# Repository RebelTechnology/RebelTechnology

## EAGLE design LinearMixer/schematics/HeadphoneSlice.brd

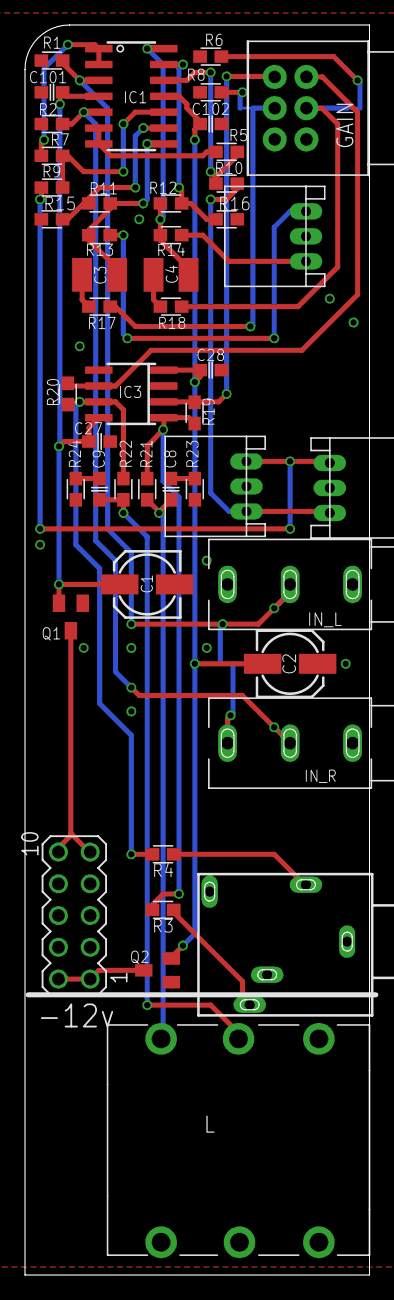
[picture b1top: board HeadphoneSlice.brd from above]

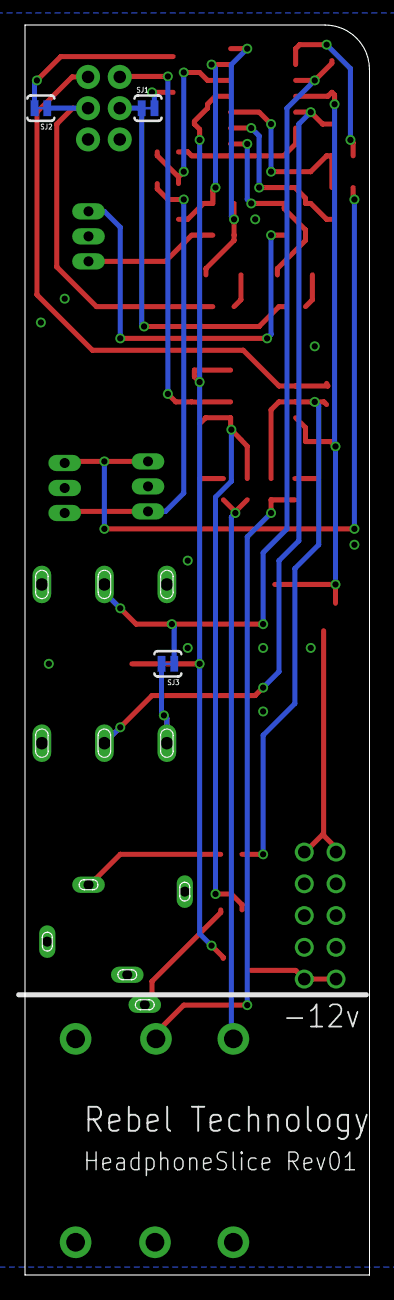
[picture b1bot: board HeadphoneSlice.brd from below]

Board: 2 copper layers, 27.5 x 100.0 mm, 50 parts (3 on the bottom side), 36 nets.

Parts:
3I, 3O, 3O2: CON-JST_PH_3W
C1, C2: 10u; 153CLV-0505
C3, C4: 1u Polyester; C1210
C8, C9: 47n; C0603
C27, C28, C101, C102: 100n; C0603
GAIN: POT-BOURNS-PTD902
IC1: QUAD_OPAMPD; SO14
IC3: RC4560; SO08
IN_L: JACK-UJ-3502-RSLOT; UJ-3502-R-SLOT
IN_R: JACK-UJ-3502-RSLOT; UJ-3502-R-SLOT
L: NEUTRIK_NMJ6HCD2; NMJ6HCD2
Q1: SI2309CDS; SOT23
Q2: BSS123; SOT23
R1, R2: 1M; 0603
R3, R4: 100R; 0603
R5, R7, R9, R10: 100k; 0603
R6, R8: 2k7; 0603
R11, R12, R15, R16, R19, R20: 10k; 0603
R13, R14: 1k; 0603
R17, R18: 22k; 0603
R21, R22: 22R; 0603
R23, R24: 10R; 0603
SJ1, SJ2, SJ3: SOLDERJUMPERTRACE; SJ_2S-TRACE
SV1: MA05-2
X1: 1503_09

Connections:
+12V: C1.+, C27.1, C101.1, IC1.4, IC3.8, Q1.2
-12V: C2.-, C28.1, C102.1, IC1.11, IC3.4, Q2.2
BUS_IN_L: 3I.P3, 3O.P1, R9.2
BUS_IN_R: 3I.P1, 3O.P3, R10.2
BUS_OUT_L: 3O2.P1, R13.2
BUS_OUT_R: 3O2.P3, R14.2
GND: 3I.P2, 3O.P2, 3O2.P2, C1.-, C2.+, C27.2, C28.2, C101.2, C102.2, GAIN.1, GAIN.4, IC3.3, IC3.5, IN_L.P$3, IN_R.P$3, L.S, L.SN, Q1.1, Q2.1, R1.2, R2.2, R6.2, R8.2, R15.1, R16.1, R23.1, R24.1, SV1.3, SV1.4, SV1.5, SV1.6, SV1.7, SV1.8, X1.1
HP_L: C8.1, L.T, R21.1
HP_R: C9.1, L.R, R22.1
IN_B1: IN_R.P$2, SJ3.2
IN_L: IC1.3, IN_L.P$1, R1.1, SJ3.1
IN_R: IC1.5, IN_R.P$1, R2.1
LINE_L: R3.1, X1.3
LINE_R: R4.1, X1.2
unnamed: Q2.3, SV1.1, SV1.2
unnamed: IC3.7, R4.2, R20.1, R22.2
unnamed: GAIN.6, IC3.2, R19.2
unnamed: C4.2, R18.2
unnamed: GAIN.5, R17.1, SJ1.1
unnamed: GAIN.2, R18.1, SJ2.1
unnamed: C4.1, IC1.14, R12.2, R14.1
unnamed: C3.2, R17.2
unnamed: R8.1, SJ1.2
unnamed: C3.1, IC1.8, R11.2, R13.1
unnamed: IC1.6, IC1.7, R5.2
unnamed: C9.2, R24.2
unnamed: IC1.1, IC1.2, R7.2
unnamed: Q1.3, SV1.9, SV1.10
unnamed: R6.1, SJ2.2
unnamed: GAIN.3, IC3.6, R20.2
unnamed: IC1.9, R11.1, R15.2
unnamed: IC1.13, R12.1, R16.2
unnamed: IC3.1, R3.2, R19.1, R21.2
unnamed: C8.2, R23.2
unnamed: IC1.12, R5.1, R10.1
unnamed: IC1.10, R7.1, R9.1

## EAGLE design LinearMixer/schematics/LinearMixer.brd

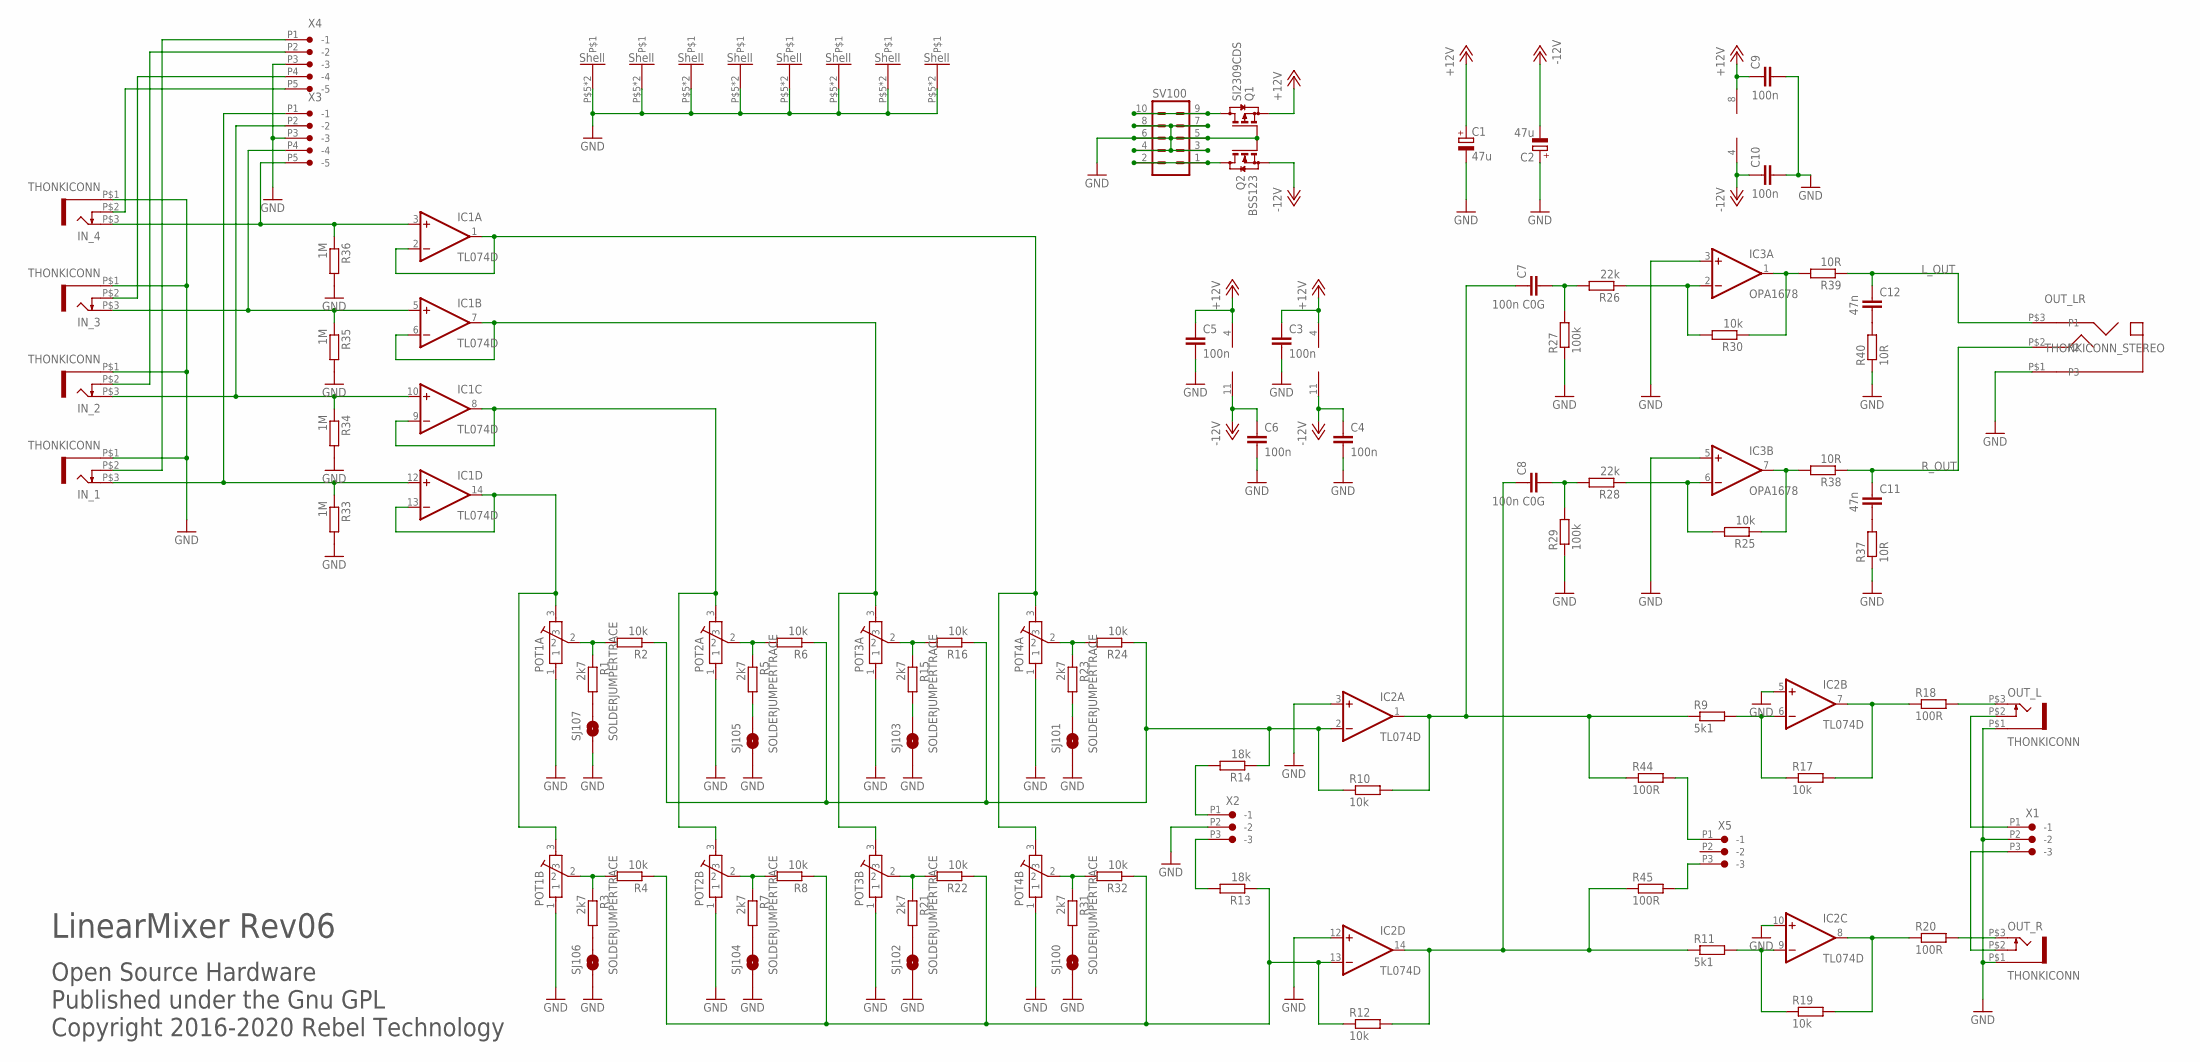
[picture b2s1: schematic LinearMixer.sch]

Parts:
C1, C2: 47u; 153CLV-0505
C3, C4, C5, C6, C9, C10: 100n; C0603
C7, C8: 100n C0G; C1210
C11, C12: 47n; C0603
IC1, IC2: TL074D; SO14
IC3: OPA1678; SO08
IN_1, IN_2, IN_3, IN_4: THONKICONN
OUT_L: THONKICONN
OUT_LR: THONKICONN_STEREO
OUT_R: THONKICONN
POT1A, POT1B, POT2A, POT2B, POT3A, POT3B, POT4A, POT4B: POT-ALPS-RK09L1140
Q1: SI2309CDS; SOT23
Q2: BSS123; SOT23
R1, R3, R5, R7, R15, R21, R23, R31: 2k7; 0603
R2, R4, R6, R8, R10, R12, R16, R17, R19, R22, R24, R25, R30, R32: 10k; 0603
R9, R11: 5k1; 0603
R13, R14: 18k; 0603
R18, R20, R44, R45: 100R; 0603
R26, R28: 22k; 0603
R27, R29: 100k; 0603
R33, R34, R35, R36: 1M; 0603
R37, R38, R39, R40: 10R; 0603
SJ100, SJ101, SJ102, SJ103, SJ104, SJ105, SJ106, SJ107: SOLDERJUMPERTRACE; SJ_2S-TRACE
SV100: MA05-2
X1, X2, X5: CON-JST_PH_3W
X3, X4: CON-JST_PH_5W

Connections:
+12V: C1.+, C3.1, C5.1, C9.1, IC1.4 (V+), IC2.4 (V+), IC3.8 (V+), Q1.2 (S)
-12V: C2.-, C4.1, C6.1, C10.1, IC1.11 (V-), IC2.11 (V-), IC3.4 (V-), Q2.2 (S)
GND: C1.-, C2.+, C3.2, C4.2, C5.2, C6.2, C9.2, C10.2, IC2.3 (+IN), IC2.5 (+IN), IC2.10 (+IN), IC2.12 (+IN), IC3.3 (+IN), IC3.5 (+IN), IN_1.P$1 (5), IN_2.P$1 (5), IN_3.P$1 (5), IN_4.P$1 (5), OUT_L.P$1 (5), OUT_LR.P$1 (P3), OUT_R.P$1 (5), POT1A.1, POT1A.P$5, POT1A.P$6, POT1B.1, POT1B.P$5, POT1B.P$6, POT2A.1, POT2A.P$5, POT2A.P$6, POT2B.1, POT2B.P$5, POT2B.P$6, POT3A.1, POT3A.P$5, POT3A.P$6, POT3B.1, POT3B.P$5, POT3B.P$6, POT4A.1, POT4A.P$5, POT4A.P$6, POT4B.1, POT4B.P$5, POT4B.P$6, Q1.1 (G), Q2.1 (G), R27.1, R29.1, R33.2, R34.2, R35.2, R36.2, R37.1, R40.1, SJ100.1, SJ101.1, SJ102.1, SJ103.1, SJ104.1, SJ105.1, SJ106.1, SJ107.1, SV100.3, SV100.4, SV100.5, SV100.6, SV100.7, SV100.8, X1.P2 (-2), X2.P2 (-2), X3.P3 (-3), X4.P3 (-3)
IN_1: IC1.12 (+IN), IN_1.P$3 (3), R33.1, X3.P1 (-1)
IN_2: IC1.10 (+IN), IN_2.P$3 (3), R34.1, X3.P2 (-2)
IN_3: IC1.5 (+IN), IN_3.P$3 (3), R35.1, X3.P4 (-4)
IN_4: IC1.3 (+IN), IN_4.P$3 (3), R36.1, X3.P5 (-5)
IN_A: R14.2, X2.P1 (-1)
IN_B: R13.2, X2.P3 (-3)
IN_SW_1: IN_1.P$2 (4), X4.P1 (-1)
IN_SW_2: IN_2.P$2 (4), X4.P2 (-2)
IN_SW_3: IN_3.P$2 (4), X4.P4 (-4)
IN_SW_4: IN_4.P$2 (4), X4.P5 (-5)
L_OUT: C12.1, OUT_LR.P$3 (P1), R39.1
unnamed: Q2.3 (D), SV100.1, SV100.2
unnamed: IC3.7 (OUT), R25.1, R38.2
unnamed: IC3.2 (-IN), R26.1, R30.2
unnamed: C8.2, R28.2, R29.2
unnamed: IC2.8 (OUT), R19.2, R20.1
unnamed: IC2.7 (OUT), R17.2, R18.1
unnamed: IC2.13 (-IN), R4.1, R8.1, R12.1, R13.1, R22.1, R32.1
unnamed: C7.2, R26.2, R27.2
unnamed: OUT_L.P$3 (3), R18.2
unnamed: C8.1, IC2.14 (OUT), R11.1, R12.2, R45.1
unnamed: IC2.2 (-IN), R2.1, R6.1, R10.1, R14.1, R16.1, R24.1
unnamed: C11.2, R37.2
unnamed: C7.1, IC2.1 (OUT), R9.1, R10.2, R44.1
unnamed: Q1.3 (D), SV100.9, SV100.10
unnamed: OUT_R.P$3 (3), R20.2
unnamed: IC3.6 (-IN), R25.2, R28.1
unnamed: R1.2, SJ107.2
unnamed: IC2.6 (-IN), R9.2, R17.1
unnamed: IC3.1 (OUT), R30.1, R39.2
unnamed: POT1B.2, R3.1, R4.2
unnamed: C12.2, R40.2
unnamed: R5.2, SJ105.2
unnamed: IC2.9 (-IN), R11.2, R19.1
unnamed: R15.2, SJ103.2
unnamed: R23.2, SJ101.2
unnamed: R3.2, SJ106.2
unnamed: IC1.8 (OUT), IC1.9 (-IN), POT2A.3, POT2B.3
unnamed: R7.2, SJ104.2
unnamed: POT1A.2, R1.1, R2.2
unnamed: POT2B.2, R7.1, R8.2
unnamed: POT3B.2, R21.1, R22.2
unnamed: R21.2, SJ102.2
unnamed: R31.2, SJ100.2
unnamed: IC1.13 (-IN), IC1.14 (OUT), POT1A.3, POT1B.3
unnamed: POT4B.2, R31.1, R32.2
unnamed: POT4A.2, R23.1, R24.2
unnamed: POT3A.2, R15.1, R16.2
unnamed: POT2A.2, R5.1, R6.2
unnamed: IC1.6 (-IN), IC1.7 (OUT), POT3A.3, POT3B.3
unnamed: IC1.1 (OUT), IC1.2 (-IN), POT4A.3, POT4B.3
OUT_NS_L: R44.2, X5.P1 (-1)
OUT_NS_R: R45.2, X5.P3 (-3)
OUT_SW_A: OUT_L.P$2 (4), X1.P1 (-1)
OUT_SW_B: OUT_R.P$2 (4), X1.P3 (-3)
R_OUT: C11.1, OUT_LR.P$2 (P2), R38.1

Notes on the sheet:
Open Source Hardware Published under the Gnu GPL Copyright 2016-2020 Rebel Technology
LinearMixer Rev06

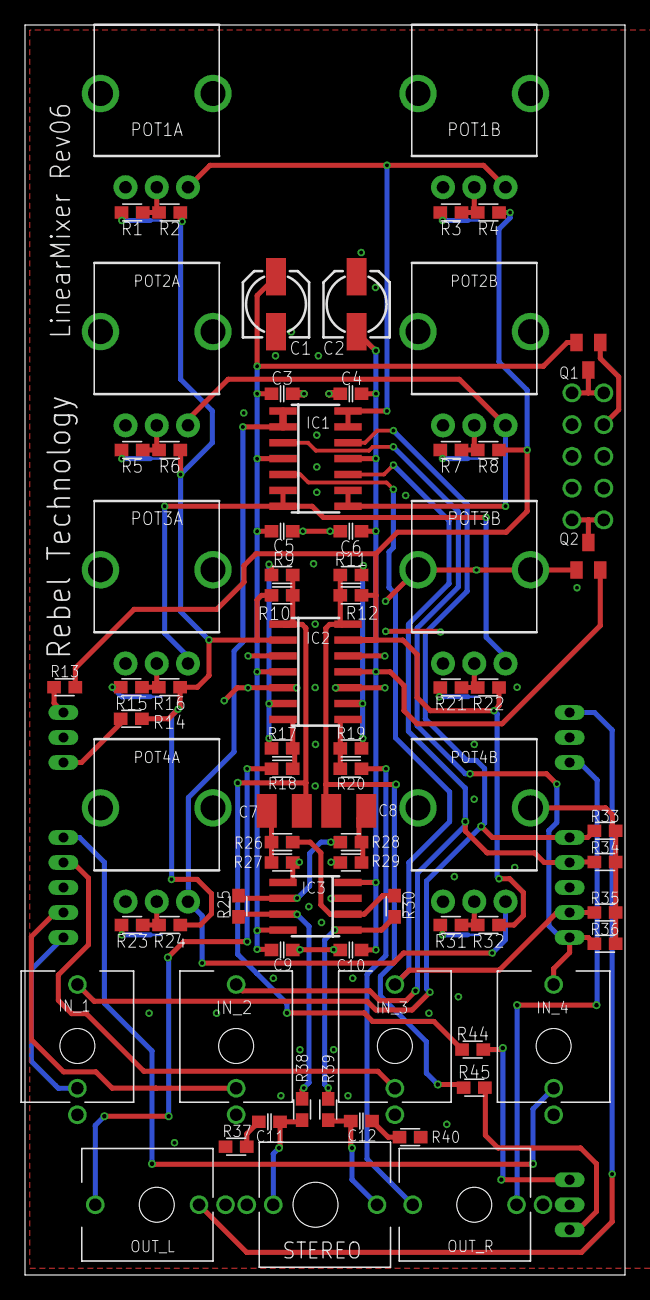
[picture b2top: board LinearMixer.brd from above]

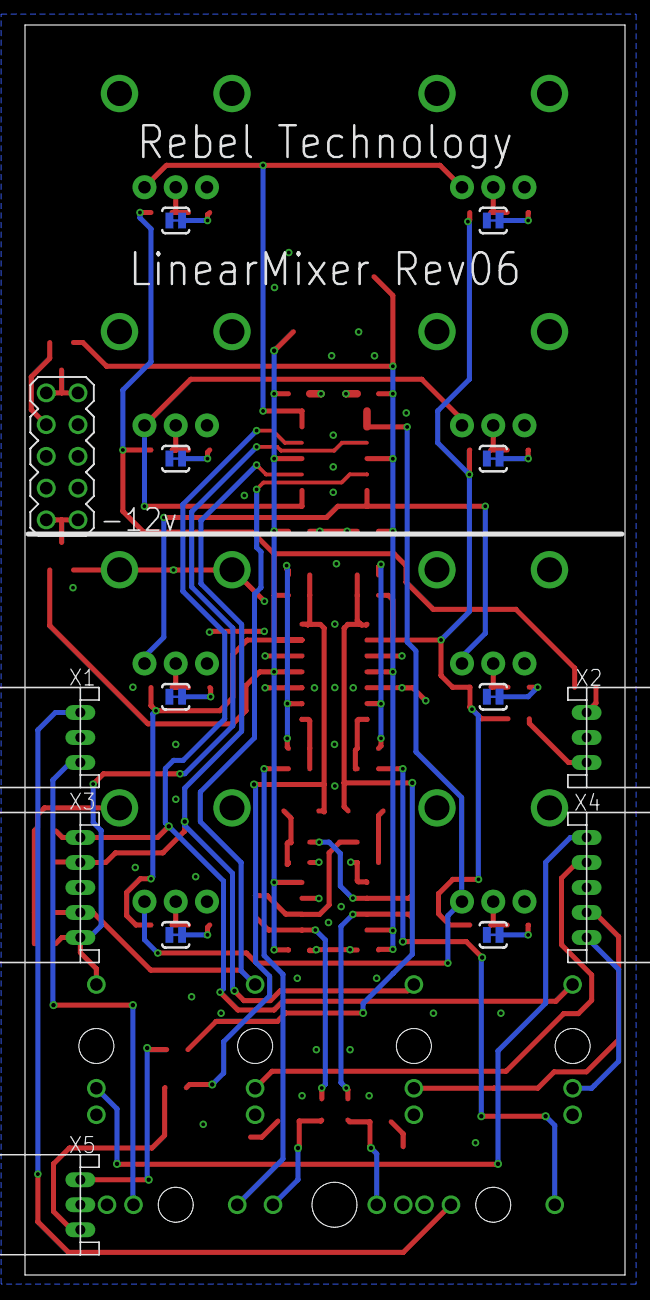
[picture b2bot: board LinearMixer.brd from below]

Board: 2 copper layers, 48.0 x 100.0 mm, 88 parts (14 on the bottom side), 59 nets.

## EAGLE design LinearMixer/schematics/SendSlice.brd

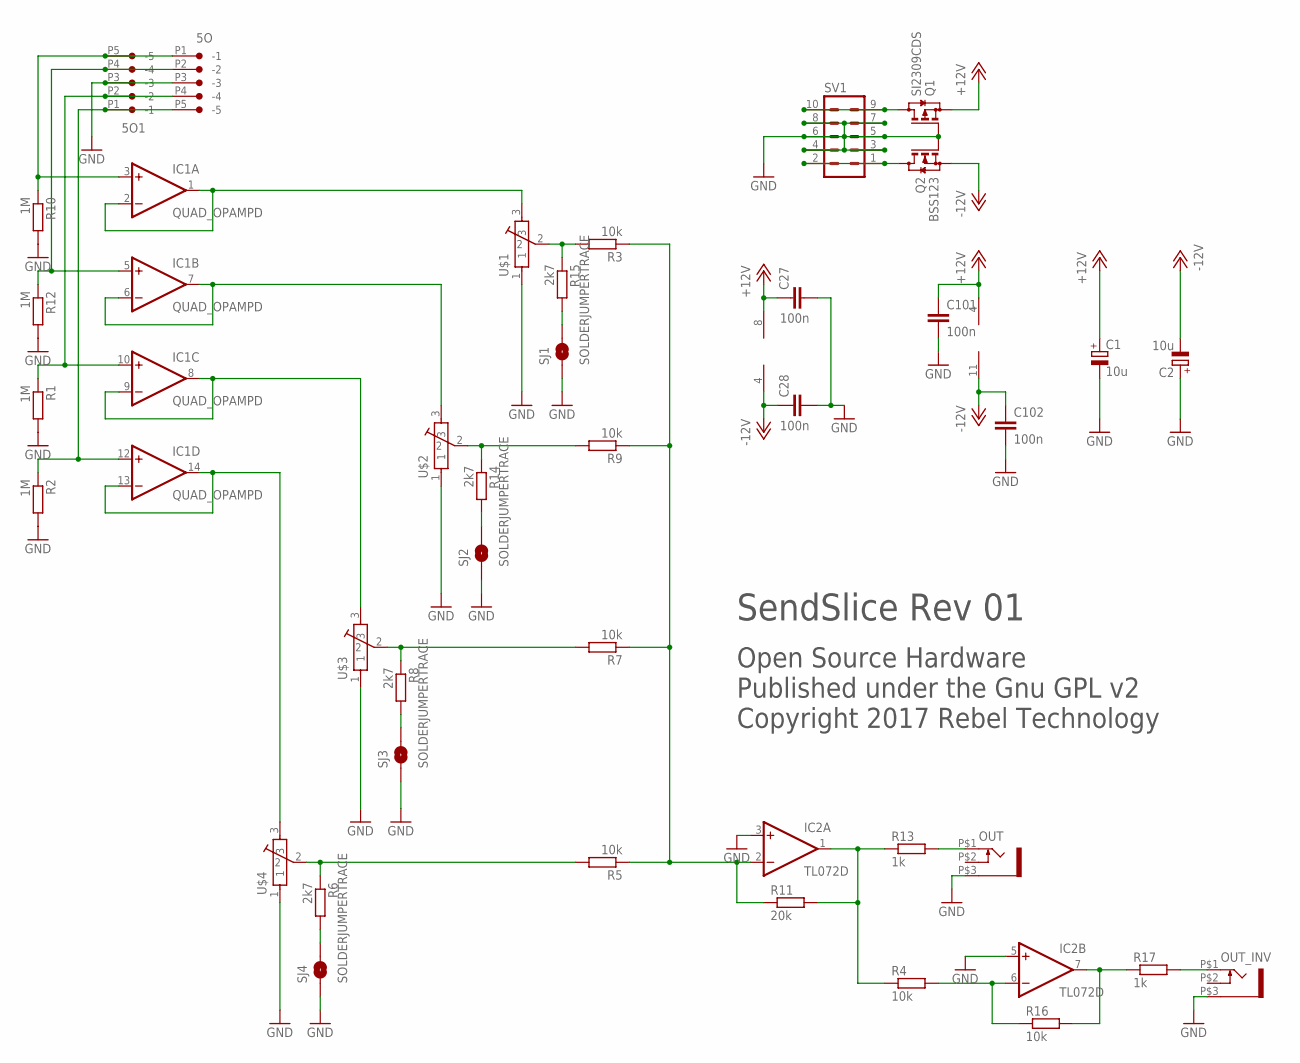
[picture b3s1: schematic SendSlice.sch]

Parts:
5O, 5O1: CON-JST_PH_5W
C1, C2: 10u; 153CLV-0505
C27, C28, C101, C102: 100n; C0603
IC1: QUAD_OPAMPD; SO14
IC2: TL072D; SO08
OUT: JACK-UJ-3502-R; UJ-3502-R
OUT_INV: JACK-UJ-3502-R; UJ-3502-R
Q1: SI2309CDS; SOT23
Q2: BSS123; SOT23
R1, R2, R10, R12: 1M; 0603
R3, R4, R5, R7, R9, R16: 10k; 0603
R6, R8, R14, R15: 2k7; 0603
R11: 20k; 0603
R13, R17: 1k; 0603
SJ1, SJ2, SJ3, SJ4: SOLDERJUMPERTRACE; SJ_2S-TRACE
SV1: MA05-2
U$1, U$2, U$3, U$4: POT-BOURNS-PTD901

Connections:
+12V: C1.+, C27.1, C101.1, IC1.4 (V+), IC2.8 (V+), Q1.2 (S)
-12V: C2.-, C28.1, C102.1, IC1.11 (V-), IC2.4 (V-), Q2.2 (S)
GND: 5O.P3 (-3), 5O1.P3 (-3), C1.-, C2.+, C27.2, C28.2, C101.2, C102.2, IC2.3 (+IN), IC2.5 (+IN), OUT.P$3 (SLEEVE), OUT_INV.P$3 (SLEEVE), Q1.1 (G), Q2.1 (G), R1.2, R2.2, R10.2, R12.2, SJ1.1, SJ2.1, SJ3.1, SJ4.1, SV1.3, SV1.4, SV1.5, SV1.6, SV1.7, SV1.8, U$1.1, U$2.1, U$3.1, U$4.1
IN_1: 5O.P5 (-5), 5O1.P1 (-1), IC1.12 (+IN), R2.1
IN_2: 5O.P4 (-4), 5O1.P2 (-2), IC1.10 (+IN), R1.1
IN_3: 5O.P2 (-2), 5O1.P4 (-4), IC1.5 (+IN), R12.1
IN_4: 5O.P1 (-1), 5O1.P5 (-5), IC1.3 (+IN), R10.1
unnamed: Q2.3 (D), SV1.1, SV1.2
unnamed: R9.2, R14.1, U$2.2
unnamed: R3.2, R15.1, U$1.2
unnamed: IC1.6 (-IN), IC1.7 (OUT), U$2.3
unnamed: IC1.1 (OUT), IC1.2 (-IN), U$1.3
unnamed: IC2.1 (OUT), R4.1, R11.2, R13.1
unnamed: IC2.7 (OUT), R16.2, R17.1
unnamed: IC2.2 (-IN), R3.1, R5.1, R7.1, R9.1, R11.1
unnamed: OUT.P$1 (TIP), R13.2
unnamed: R15.2, SJ1.2
unnamed: IC1.13 (-IN), IC1.14 (OUT), U$4.3
unnamed: R6.2, SJ4.2
unnamed: IC1.8 (OUT), IC1.9 (-IN), U$3.3
unnamed: Q1.3 (D), SV1.9, SV1.10
unnamed: R8.2, SJ3.2
unnamed: R14.2, SJ2.2
unnamed: IC2.6 (-IN), R4.2, R16.1
unnamed: OUT_INV.P$1 (TIP), R17.2
unnamed: R5.2, R6.1, U$4.2
unnamed: R7.2, R8.1, U$3.2

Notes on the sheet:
Open Source Hardware Published under the Gnu GPL v2 Copyright 2017 Rebel Technology
SendSlice Rev 01

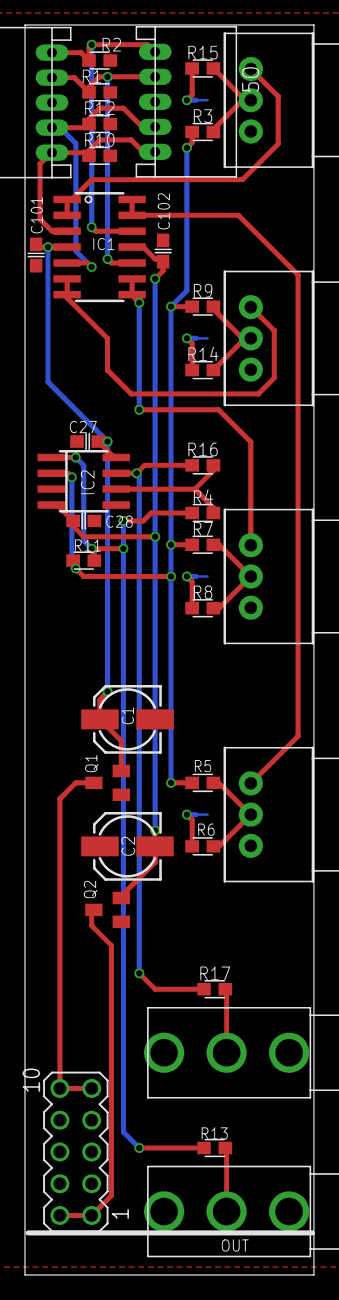
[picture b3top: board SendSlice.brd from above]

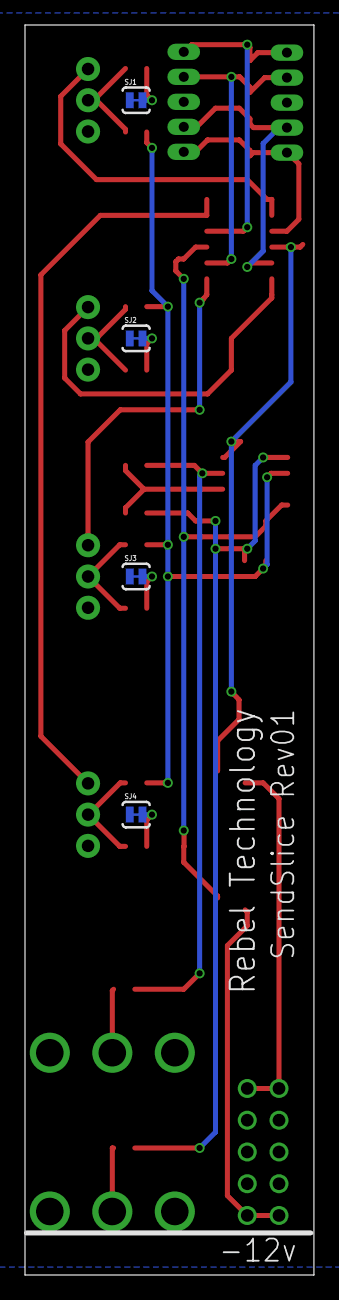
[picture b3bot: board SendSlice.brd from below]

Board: 2 copper layers, 23.1 x 100.0 mm, 40 parts (4 on the bottom side), 27 nets.

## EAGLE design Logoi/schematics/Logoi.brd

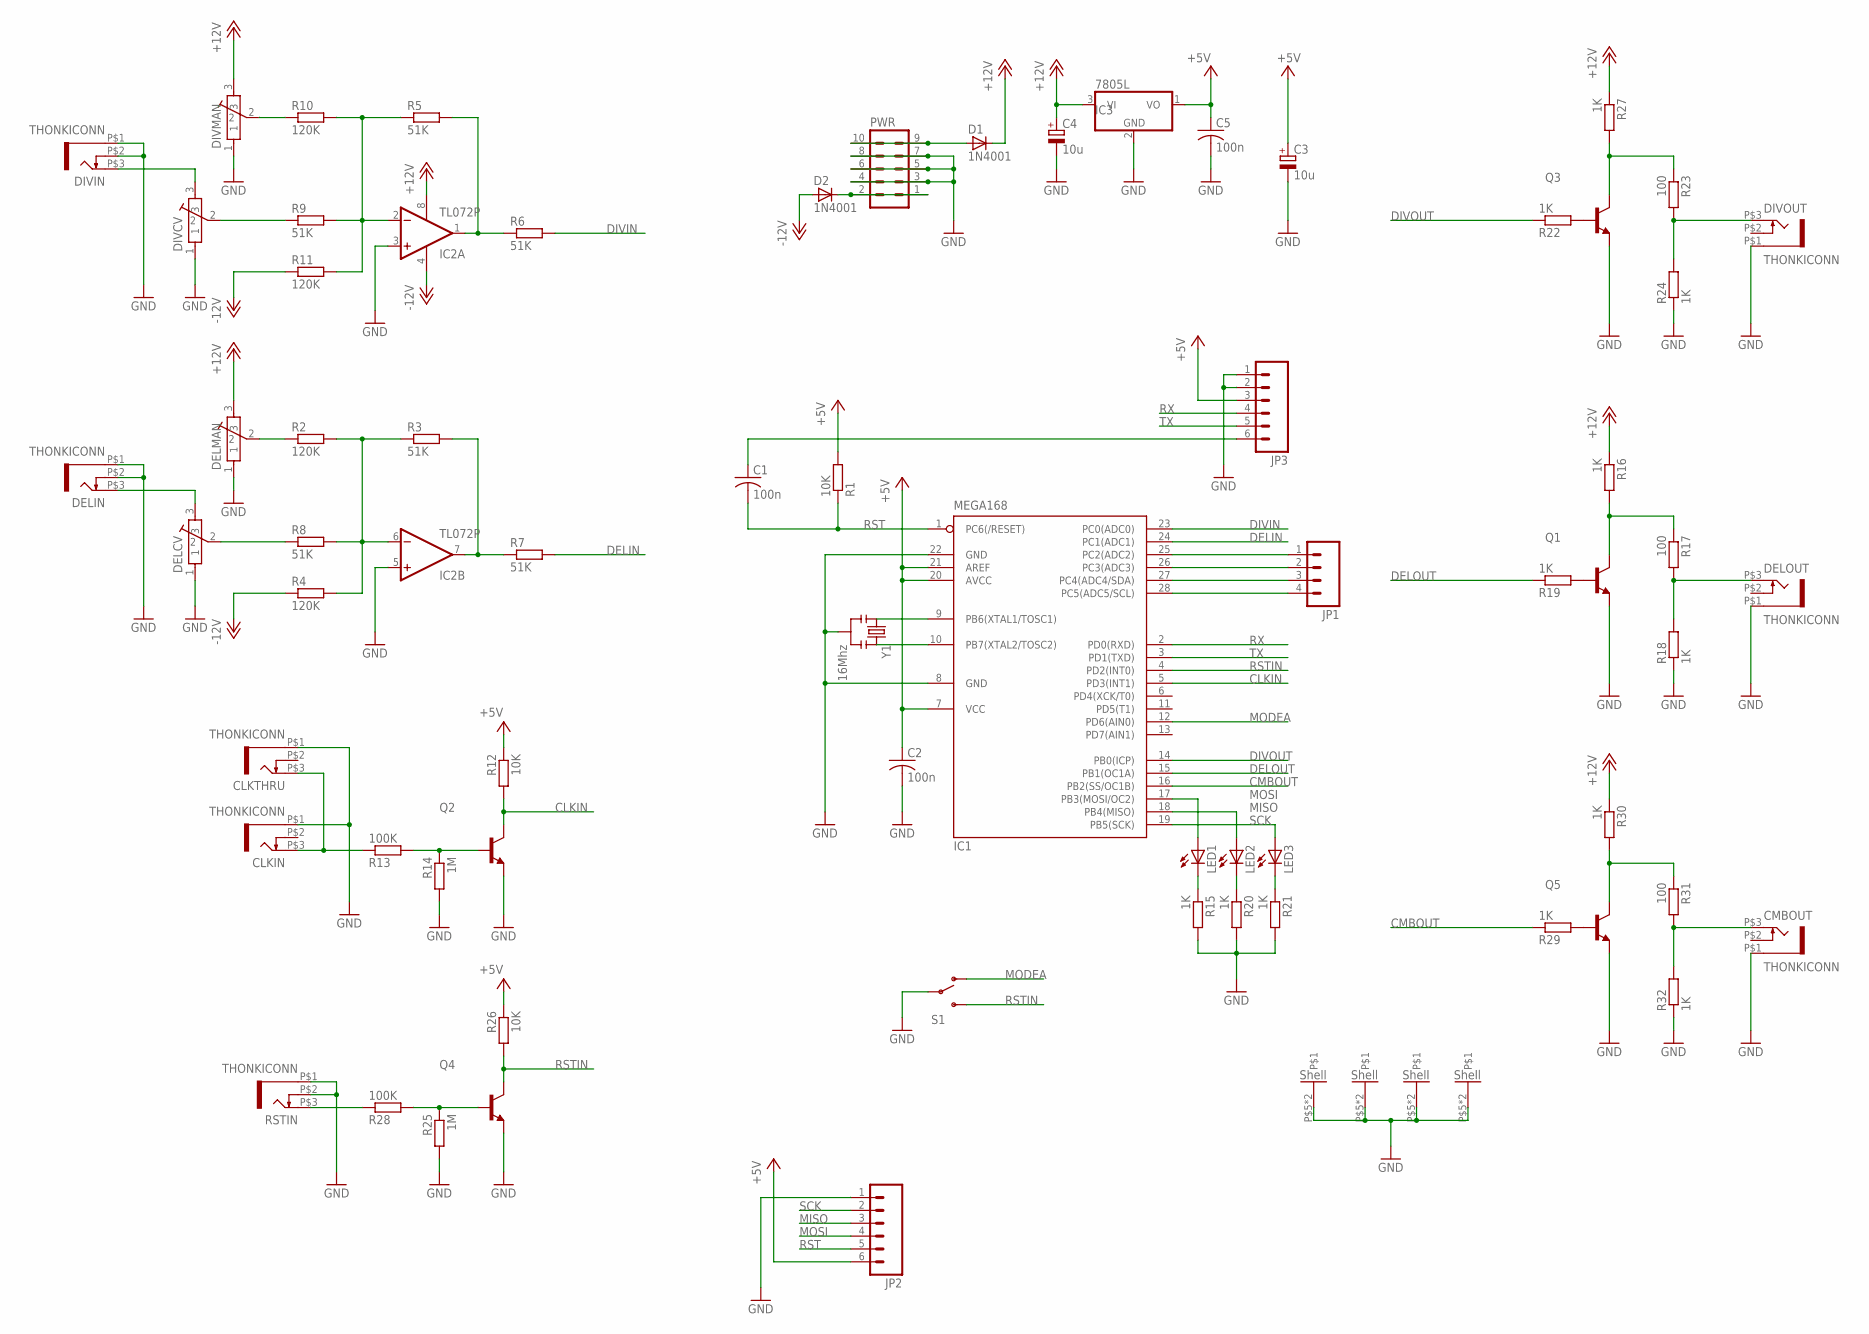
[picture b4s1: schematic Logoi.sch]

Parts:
C1, C2, C5: 100n; C050-024X044
C3, C4: 10u; E5-6
CLKIN: THONKICONN
CLKTHRU: THONKICONN
CMBOUT: THONKICONN
D1, D2: 1N4001; DIODE-1N4001
DELCV: POT-ALPS-RK09L1140
DELIN: THONKICONN
DELMAN: POT-ALPS-RK09L1140
DELOUT: THONKICONN
DIVCV: POT-ALPS-RK09L1140
DIVIN: THONKICONN
DIVMAN: POT-ALPS-RK09L1140
DIVOUT: THONKICONN
IC1: MEGA168; DIL28-3
IC2: TL072P; DIL08
IC3: 7805L; TO92
JP1: M04PTH; 1X04
JP2, JP3: M06SIP; 1X06
LED1, LED2, LED3: LED3MM
PWR: MA05-2
Q1, Q2, Q3, Q4, Q5: 2N3904-NPN-TO92-EBC; TO92-EBC
R1, R12, R26: 10K; 0204/7
R2, R4, R10, R11: 120K; 0204/7
R3, R5, R6, R7, R8, R9: 51K; 0204/7
R13, R28: 100K; 0204/7
R14, R25: 1M; 0204/7
R15, R16, R18, R19, R20, R21, R22, R24, R27, R29, R30, R32: 1K; 0204/7
R17, R23, R31: 100; 0204/7
RSTIN: THONKICONN
S1: SWITCH-SPST; SWITCH-SPDT-SALECOM-T8014
Y1: 16Mhz; RESONATOR-PTH

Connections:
+5V: C2.1, C3.+, C5.1, IC1.7 (VCC), IC1.20 (AVCC), IC1.21 (AREF), IC3.1 (VO), JP2.6, JP3.3, R1.2, R12.1, R26.1
+12V: C4.+, D1.C, DELMAN.3, DIVMAN.3, IC2.8 (V+), IC3.3 (VI), R16.1, R27.1, R30.1
-12V: D2.A, IC2.4 (V-), R4.1, R11.1
CLKIN: IC1.5 (PD3(INT1)), Q2.C, R12.2
CMBOUT: IC1.16 (PB2(SS/OC1B)), R29.1
DELIN: IC1.24 (PC1(ADC1)), R7.2
DELOUT: IC1.15 (PB1(OC1A)), R19.1
DIVIN: IC1.23 (PC0(ADC0)), R6.2
DIVOUT: IC1.14 (PB0(ICP)), R22.1
GND: C2.2, C3.-, C4.-, C5.2, CLKIN.P$1 (5), CLKTHRU.P$1 (5), CMBOUT.P$1 (5), DELCV.1, DELCV.P$5, DELCV.P$6, DELIN.P$1 (5), DELIN.P$2 (4), DELMAN.1, DELMAN.P$5, DELMAN.P$6, DELOUT.P$1 (5), DIVCV.1, DIVCV.P$5, DIVCV.P$6, DIVIN.P$1 (5), DIVIN.P$2 (4), DIVMAN.1, DIVMAN.P$5, DIVMAN.P$6, DIVOUT.P$1 (5), IC1.8 (GND), IC1.22 (GND), IC2.3 (+IN), IC2.5 (+IN), IC3.2 (GND), JP2.1, JP3.1, JP3.2, PWR.3, PWR.4, PWR.5, PWR.6, PWR.7, PWR.8, Q1.E, Q2.E, Q3.E, Q4.E, Q5.E, R14.2, R15.2, R18.1, R20.2, R21.2, R24.1, R25.2, R32.1, RSTIN.P$1 (5), RSTIN.P$2 (4), S1.2, Y1.2
MISO: IC1.18 (PB4(MISO)), JP2.3, LED2.A
MODEA: IC1.12 (PD6(AIN0)), S1.1 (O)
MOSI: IC1.17 (PB3(MOSI/OC2)), JP2.4, LED1.A
unnamed: DIVCV.3, DIVIN.P$3 (3)
unnamed: IC2.2 (-IN), R5.1, R9.2, R10.2, R11.2
unnamed: DIVMAN.2, R10.1
unnamed: IC2.1 (OUT), R5.2, R6.1
unnamed: DIVCV.2, R9.1
unnamed: D1.A, PWR.9, PWR.10
unnamed: IC2.6 (-IN), R2.2, R3.1, R4.2, R8.2
unnamed: DELMAN.2, R2.1
unnamed: IC2.7 (OUT), R3.2, R7.1
unnamed: DELCV.2, R8.1
unnamed: IC1.25 (PC2(ADC2)), JP1.1
unnamed: DELCV.3, DELIN.P$3 (3)
unnamed: IC1.26 (PC3(ADC3)), JP1.2
unnamed: IC1.27 (PC4(ADC4/SDA)), JP1.3
unnamed: IC1.28 (PC5(ADC5/SCL)), JP1.4
unnamed: IC1.9 (PB6(XTAL1/TOSC1)), Y1.1
unnamed: IC1.10 (PB7(XTAL2/TOSC2)), Y1.3
unnamed: LED1.K (C), R15.1
unnamed: LED2.K (C), R20.1
unnamed: LED3.K (C), R21.1
unnamed: Q1.B, R19.2
unnamed: Q2.B, R13.2, R14.1
unnamed: CLKIN.P$3 (3), CLKTHRU.P$3 (3), R13.1
unnamed: C1.1, JP3.6
unnamed: DELOUT.P$3 (3), R17.2, R18.2
unnamed: Q4.B, R25.1, R28.2
unnamed: Q1.C, R16.2, R17.1
unnamed: Q3.B, R22.2
unnamed: Q5.B, R29.2
unnamed: CMBOUT.P$3 (3), R31.2, R32.2
unnamed: DIVOUT.P$3 (3), R23.2, R24.2
unnamed: Q3.C, R23.1, R27.2
unnamed: Q5.C, R30.2, R31.1
unnamed: R28.1, RSTIN.P$3 (3)
unnamed: D2.C, PWR.1, PWR.2
RST: C1.2, IC1.1 (PC6(/RESET)), JP2.5, R1.1
RSTIN: IC1.4 (PD2(INT0)), Q4.C, R26.2, S1.3 (S)
RX: IC1.2 (PD0(RXD)), JP3.4
SCK: IC1.19 (PB5(SCK)), JP2.2, LED3.A
TX: IC1.3 (PD1(TXD)), JP3.5

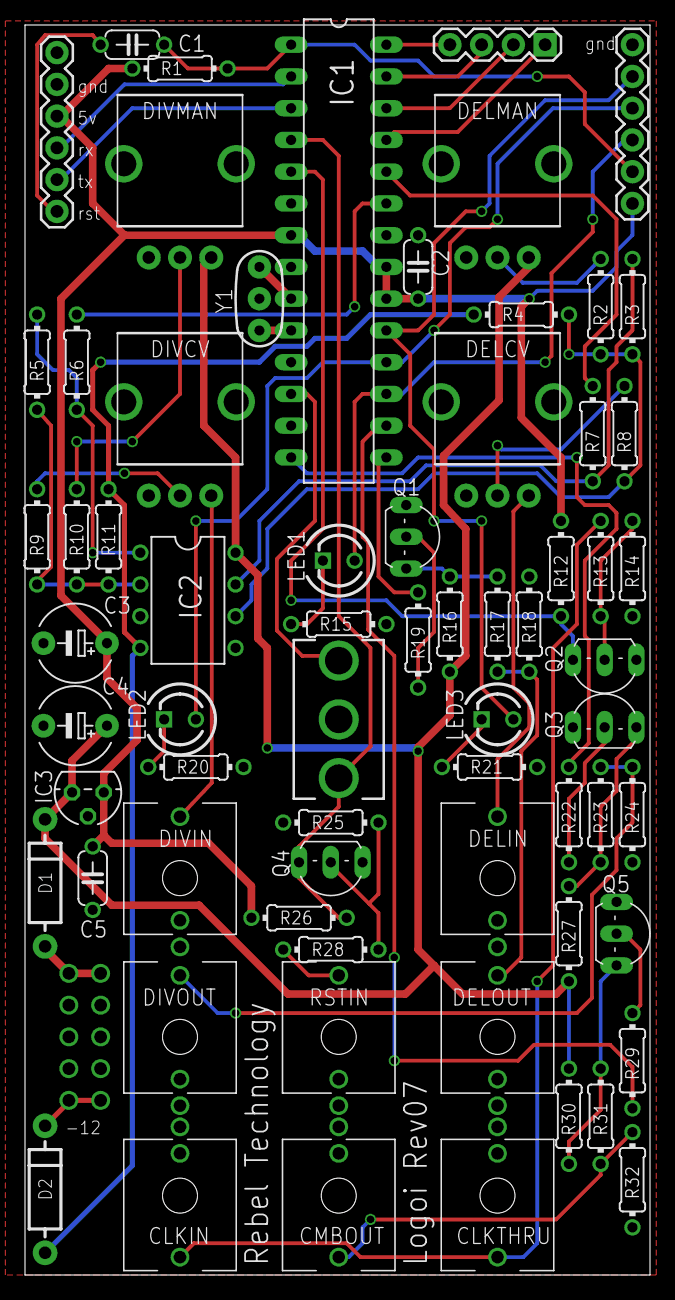
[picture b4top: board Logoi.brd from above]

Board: 2 copper layers, 50.0 x 100.0 mm, 68 parts (1 on the bottom side), 53 nets.

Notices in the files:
Magus/schematics/Magus.sch:
Copyright Rebel Technology 2019
parts and their libraries:
SparkFun: Licensing: CC v3.0 Share-Alike You are welcome to use this library for commercial purposes.
SparkFun-Connectors: Licensing: Creative Commons ShareAlike 4.0 International - https://creativecommons.org/licenses/by-sa/4.0
